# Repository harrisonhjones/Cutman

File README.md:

#Cutman#
A simple nichrome-wire cutdown board for a high altitude balloon project

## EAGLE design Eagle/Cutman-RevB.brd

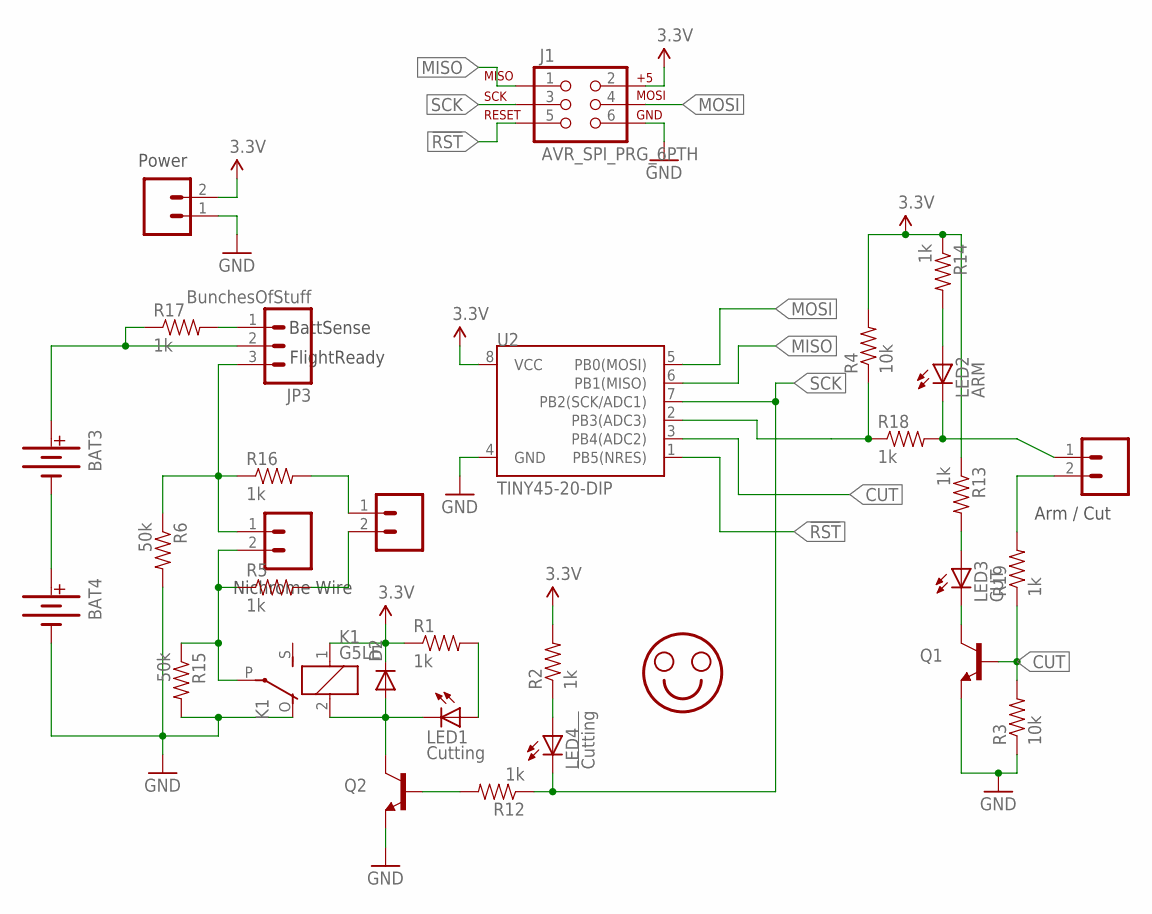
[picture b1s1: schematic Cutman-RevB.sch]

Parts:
BAT3, BAT4: BATTERYAA-KIT; BATTERY-AA-KIT
D2: DIODEPTH; DIODE-1N4001
J1: AVR_SPI_PRG_6PTH; 2X3
JP1: NichromeWire; SCREWTERMINAL-3.5MM-2_LOCK
JP2: Power; SCREWTERMINAL-3.5MM-2_LOCK
JP3: BunchesOfStuff; SCREWTERMINAL-3.5MM-3
JP4: VSense; SCREWTERMINAL-3.5MM-2_LOCK
JP6: Arm/Cut; SCREWTERMINAL-3.5MM-2_LOCK
K1: G5LE
LED1: Cutting; LED5MM
LED2: ARM; LED5MM
LED3: CUT; LED5MM
LED4: !Cutting; LED5MM
Q1, Q2: TRANSISTOR_NPNTO92; TO-92
R1, R2, R5, R12, R13, R14, R16, R17, R18, R19: 1k; AXIAL-0.3
R3, R4: 10k; AXIAL-0.3
R6, R15: 50k; AXIAL-0.3
STANDOFF2, STANDOFF3: STAND-OFF
U2: TINY45-20-DIP; DIP08

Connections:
3.3V: D2.C, J1.2, JP2.2, K1.1, R1.P$1 (1), R2.P$2 (2), R4.P$2 (2), R13.P$1 (1), R14.P$1 (1), U2.8 (VCC)
!RST: J1.5, U2.1 (PB5(NRES))
AFTERNICHROME: JP4.2, R5.P$2 (2)
ARM: R4.P$1 (1), R18.P$1 (1), U2.2 (PB3(ADC3))
BEFORENICHROME: JP4.1, R16.P$2 (2)
CUT: Q1.2 (B), R3.P$2 (2), R19.P$1 (1), U2.3 (PB4(ADC2))
GND: BAT4.GND@1 (-), BAT4.GND@2 (-), J1.6, JP2.1, K1.O, Q1.1 (E), Q2.1 (E), R3.P$1 (1), R6.P$2 (2), R15.P$2 (2), U2.4 (GND)
MISO: J1.1, U2.6 (PB1(MISO))
MOSI: J1.4, U2.5 (PB0(MOSI))
unnamed: JP1.1, JP3.3, R6.P$1 (1), R16.P$1 (1)
unnamed: JP1.2, K1.P, R5.P$1 (1), R15.P$1 (1)
unnamed: LED1.A, R1.P$2 (2)
unnamed: JP3.1, R17.P$2 (2)
unnamed: BAT3.PWR@1 (+), BAT3.PWR@2 (+), JP3.2, R17.P$1 (1)
unnamed: LED4.A, R2.P$1 (1)
unnamed: LED2.A, R14.P$2 (2)
unnamed: JP6.1, LED2.K (C), R18.P$2 (2)
unnamed: JP6.2, R19.P$2 (2)
unnamed: BAT3.GND@1 (-), BAT3.GND@2 (-), BAT4.PWR@1 (+), BAT4.PWR@2 (+)
unnamed: D2.A, K1.2, LED1.K (C), Q2.3 (C)
unnamed: LED3.K (C), Q1.3 (C)
unnamed: Q2.2 (B), R12.P$2 (2)
unnamed: LED3.A, R13.P$2 (2)
SCK: J1.3, LED4.K (C), R12.P$1 (1), U2.7 (PB2(SCK/ADC1))

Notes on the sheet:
Nichrome Wire
BattSense
FlightReady
Arm / Cut
Power

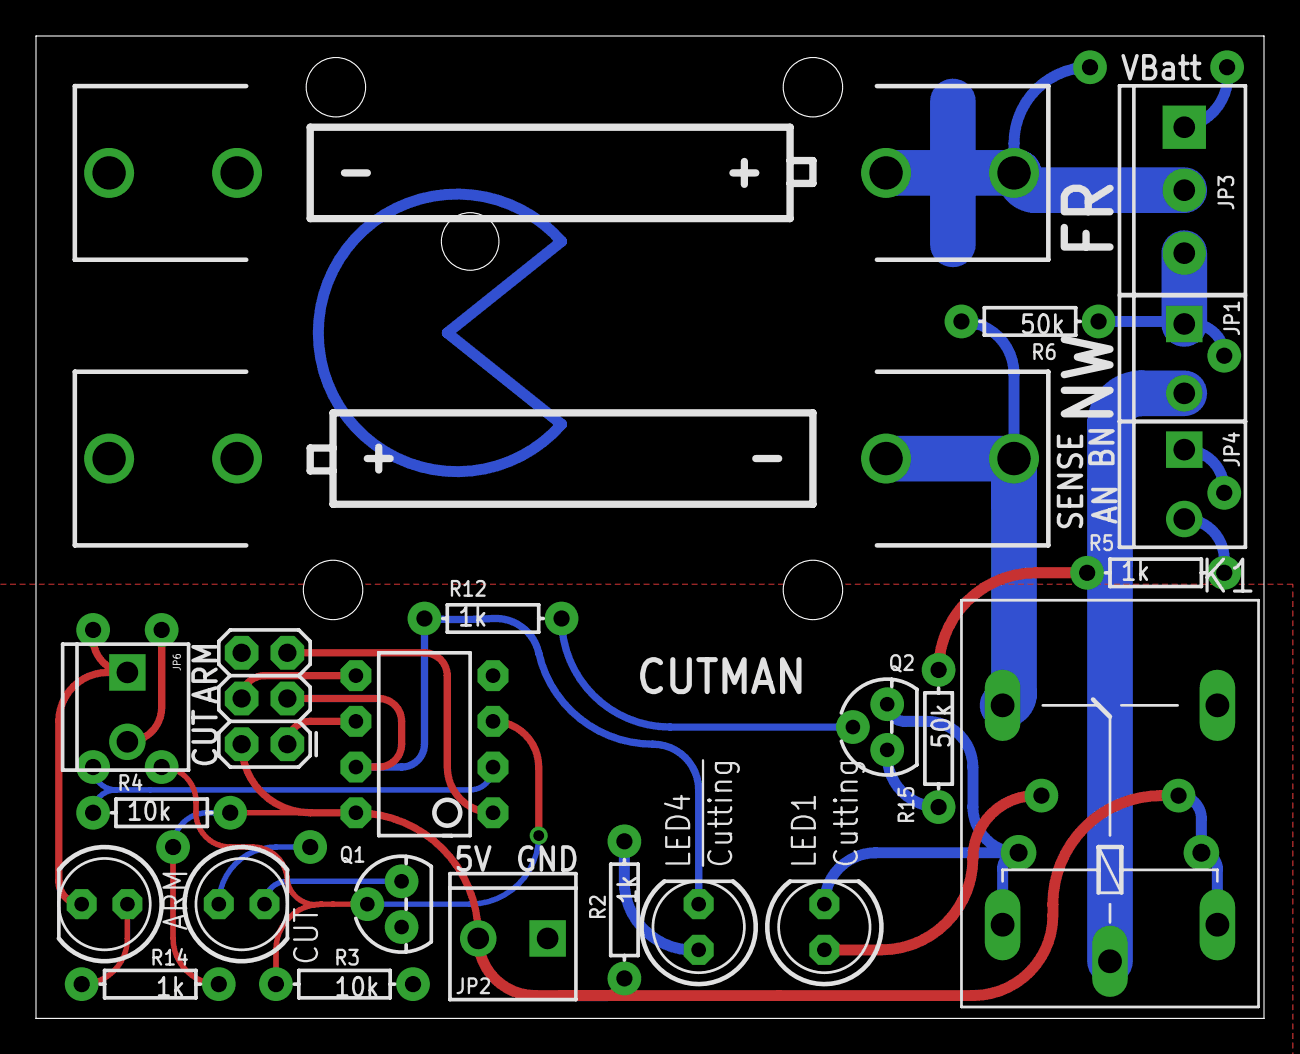
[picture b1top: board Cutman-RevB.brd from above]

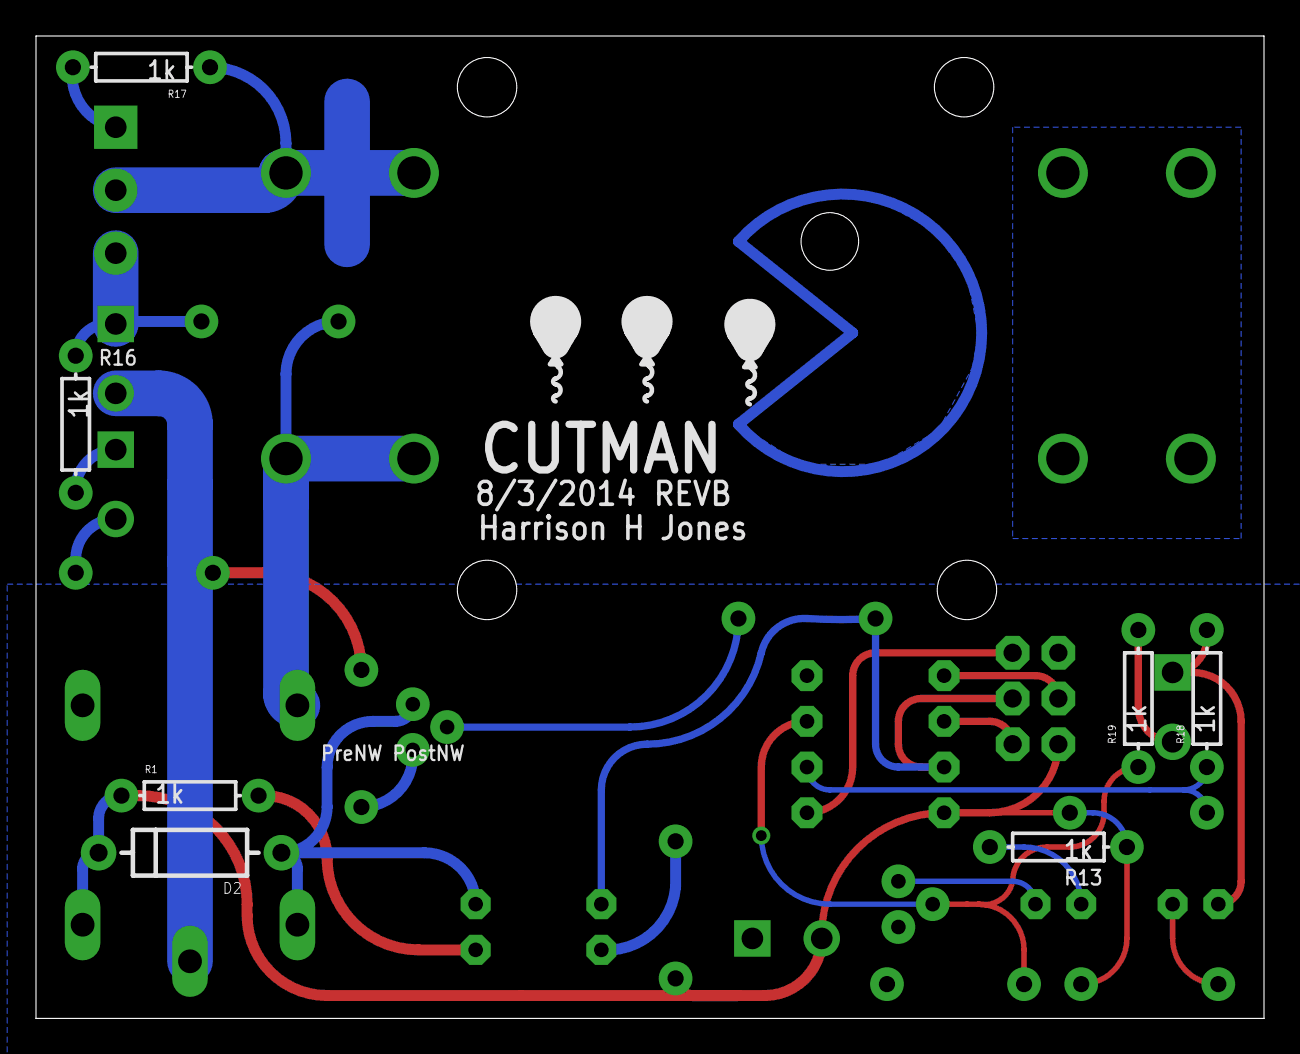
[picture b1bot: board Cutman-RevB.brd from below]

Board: 2 copper layers, 68.2 x 54.6 mm, 35 parts (7 on the bottom side), 24 nets.

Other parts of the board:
STANDOFF1, STANDOFF4: STAND-OFF

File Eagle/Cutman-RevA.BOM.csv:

"Qty";"Value";"Device";"Package";"Parts";"Description";"PROD_ID";"VALUE";
"2";"";"BATTERYAA-KIT";"BATTERY-AA-KIT";"BAT3, BAT4";"Battery Holders";"BATT-08316";"";
"1";"";"DIODEPTH";"DIODE-1N4001";"D2";"Diode";"";"";
"2";"";"TRANSISTOR_NPNTO92";"TO-92";"Q1, Q2";"Generic NPN BJT";"";"";
"1";"!Cutting";"LED5MM";"LED5MM";"LED4";"LED";"";"";
"2";"10k";"RESISTORAXIAL-0.3";"AXIAL-0.3";"R3, R4";"Resistor";"";"";
"1";"1k";"R-US_0309/V";"0309V";"R7";"RESISTOR, American symbol";"";"";
"9";"1k";"RESISTORAXIAL-0.3";"AXIAL-0.3";"R1, R2, R12, R13, R14, R16, R17, R18, R19";"Resistor";"";"";
"2";"50k";"RESISTORAXIAL-0.3";"AXIAL-0.3";"R6, R15";"Resistor";"";"";
"1";"ARM";"LED5MM";"LED5MM";"LED2";"LED";"";"";
"1";"AVR_SPI_PRG_6PTH";"AVR_SPI_PRG_6PTH";"2X3";"J1";"AVR ISP 6 Pin";"";"";
"1";"Arm/Cut";"M023.5MM_LOCK";"SCREWTERMINAL-3.5MM-2_LOCK";"JP6";"Standard 2-pin 0.1" header. Use with";"";"";
"1";"BunchesOfStuff";"M03SCREW";"SCREWTERMINAL-3.5MM-3";"JP3";"Header 3";"";"";
"1";"CUT";"LED5MM";"LED5MM";"LED3";"LED";"";"";
"1";"Cutting";"LED5MM";"LED5MM";"LED1";"LED";"";"";
"1";"NichromeWire";"M023.5MM_LOCK";"SCREWTERMINAL-3.5MM-2_LOCK";"JP1";"Standard 2-pin 0.1" header. Use with";"";"";
"1";"Power";"M023.5MM_LOCK";"SCREWTERMINAL-3.5MM-2_LOCK";"JP2";"Standard 2-pin 0.1" header. Use with";"";"";
"1";"RELAYPTH4";"RELAYPTH4";"RELAY-JZC";"U$1";"SPDT relay (COM-00101)";"";"";
"2";"STAND-OFF";"STAND-OFF";"STAND-OFF";"STANDOFF1, STANDOFF2";"#4 Stand Off";"";"";
"1";"TINY45-20-DIP";"ATTINY45TINY45-20-DIP";"DIP08";"U2";"Atmel 8-pin 2/4/8kB flash uC";"IC-09439";"TINY45-20-DIP";
"1";"VSense";"M023.5MM_LOCK";"SCREWTERMINAL-3.5MM-2_LOCK";"JP4";"Standard 2-pin 0.1" header. Use with";"";"";

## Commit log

2014-08-03 Added EAGLE save files and preference/config files to the .gitignore
2014-08-03 Initial commit of Eagle files
2014-08-03 Added a rendering of the back side of the PCB as rendered by OSH Park fab house.
2014-08-04 Revision B. In order to fix the relay footprint several bits of the board were moved around. Closes #5. Closes #3
2014-08-04 Added Window's folder thumbnail database to the ignore
2014-08-04 Added renders for the top and bottom of the RevB board
2014-08-04 Moved the description text on the bottom of the board to a new location so it is more clear and does not overlap holes & vias
2014-08-04 Added preliminary state machine

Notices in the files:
parts and their libraries:
SparkFun-DigitalIC: Licensing: CC v3.0 Share-Alike You are welcome to use this library for commercial purposes.
